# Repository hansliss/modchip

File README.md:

# modchip
This a PCB design and ASM code for a Playstation modchip based on the tiny AVR AT90S1200.

Apart from the SSOP-20 chip, it uses two MicroMatch connectors (6-pin and 8-pin straight male through-hole mount), a Murata resonator, a LED, a capacitor and a pushbutton.

Note that everything except the MicroMatch connectors are mounted on the *rear* side!

The code wasn't properly version-tracked when I did this, so there are several different ASM files, of different age and for different uses. Figure it out!

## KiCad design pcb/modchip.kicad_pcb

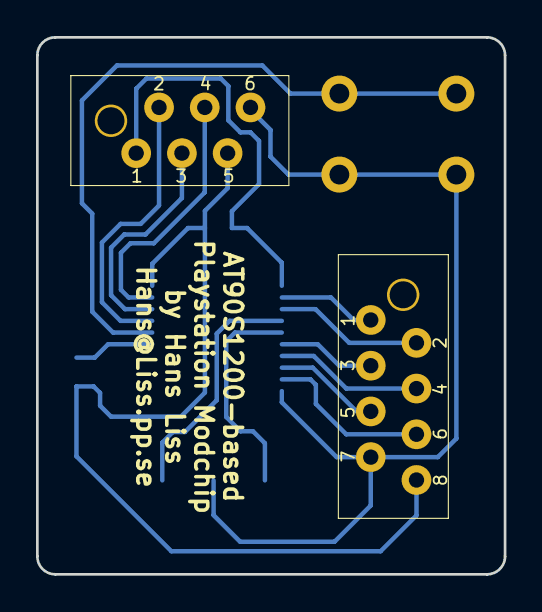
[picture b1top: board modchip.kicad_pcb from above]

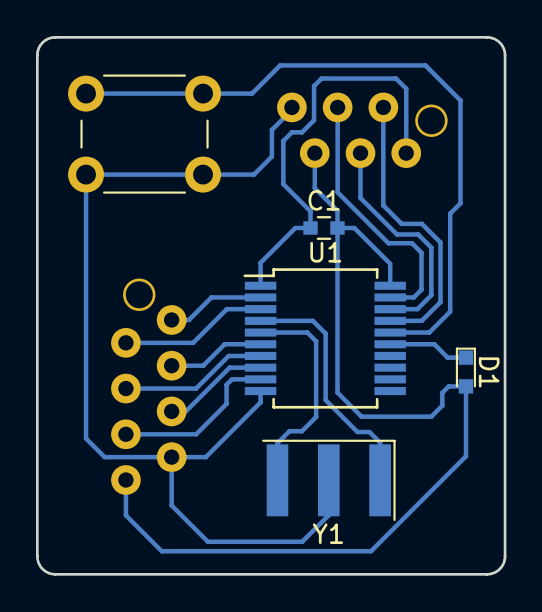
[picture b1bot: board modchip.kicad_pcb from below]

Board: 2 copper layers, 26.0 x 29.8 mm, 7 parts (5 on the bottom side), 16 nets.

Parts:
C1: C; C_0603
D1: LED; LED_0603
J1: Conn_02x04_Odd_Even; MicroMatch_FOB_TH_08P
J2: Conn_02x03_Odd_Even; MicroMatch_FOB_TH_06P
SW1: SW_Push; SW_PUSH_6mm
U1: AT90S1200-4YC; SSOP-20_5.3x7.2mm_Pitch0.65mm
Y1: Resonator; Resonator_SMD_muRata_SFECV-3pin_6.9x2.9mm

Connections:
GND: J1.7, J2.6, SW1.2, U1.10, Y1.2
unnamed: C1.1, J2.1, U1.1
unnamed: D1.1, U1.15
unnamed: J1.1, U1.2
unnamed: J1.2, U1.3
unnamed: J1.3, U1.6
unnamed: J1.4, U1.7
unnamed: J1.5, U1.8
unnamed: J1.6, U1.9
unnamed: J2.2, U1.17
unnamed: J2.3, U1.18
unnamed: J2.4, U1.19
unnamed: SW1.1, U1.16
unnamed: U1.4, Y1.1
unnamed: U1.5, Y1.3
VCC: C1.2, D1.2, J1.8, J2.5, U1.20

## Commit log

2003-03-08 Initial Import
2003-03-08 Standard project directories initialized by cvs2svn.
2018-07-17 Removed binary files and log files
2018-07-17 Moved ASM code to its own subdirectory
2018-07-17 Added KiCAD design and README
2018-07-17 Added Gerber plot files
